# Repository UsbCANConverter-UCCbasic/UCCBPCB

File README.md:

# PCB for UsbCANConverterBasic
This is PCB for UsbCANConverter basic, designed in free software KiCad.
#License
UsbCANConverterBasic is free software: you can redistribute it and/or modify it under the terms of the GNU Lesser General Public License as published by the Free Software Foundation, either version 3 of the License, or (at your option) any later version. Project is distributed in the hope that it will be useful, but WITHOUT ANY WARRANTY; without even the implied warranty of MERCHANTABILITY or FITNESS FOR A PARTICULAR PURPOSE. See the GNU Lesser General Public License for more details.

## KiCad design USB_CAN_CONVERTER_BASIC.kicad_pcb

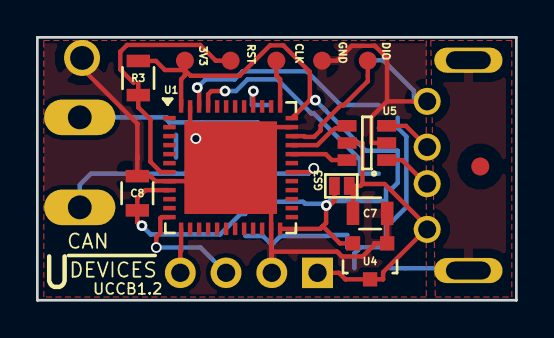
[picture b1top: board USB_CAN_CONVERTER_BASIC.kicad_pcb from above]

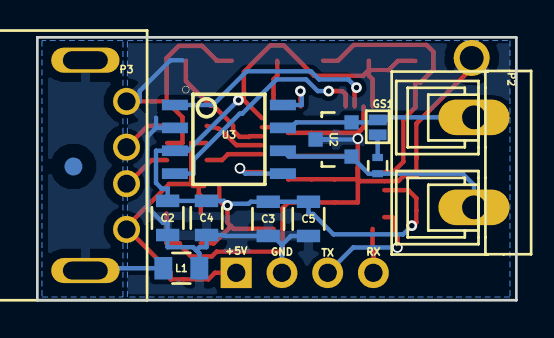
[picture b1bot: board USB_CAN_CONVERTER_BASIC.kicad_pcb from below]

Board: 2 copper layers, 26.6 x 14.6 mm, 22 parts (11 on the bottom side), 20 nets.

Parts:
C2: 100n; R_0805
C3: 10u; R_0805
C4: 10nC; R_0805
C5: 100nC; R_0805
C7, C8: 1uC; R_0805
F1: fiducial; Fiducial_1mm_Dia_2.54mm_Outer_CopperTop
F2: fiducial; Fiducial_1mm_Dia_2.54mm_Outer_CopperBottom
GS1, GS3: GS2; GS2s
L1: 30R@100MHz; C_0805
P1: CONN_01X05; swd_smd_conn5
P2: CONN_01X02; AK300-2MIRROR
P3: USB_A; USB_A_DS1097R
P4: CONN_01X04; Pin_Header_Angled_1x04m
R3: 10k; R_0805
R4: 60R; R_0402
U1: STM32F042C6Ux; QFN-48-1EP_7x7mm_Pitch0.5mm
U2: PSD2CAN; SOT-23
U3: TCAN332; SO
U4: MCP1700T-3302E/TT; SOT-23
U5: USBLC6-2; SOT-23-6

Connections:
+3V3: C2.1, C3.1, C4.1, C5.1, C8.1, GS3.2, P1.1, R3.2, U1.9, U1.24, U1.36, U1.48, U3.3, U4.2
+5V: C7.1, GS3.1, P3.1, P4.1, U4.3, U5.5
/USART_RX: P4.4, U1.13
/USART_TX: P4.3, U1.12
CAN_MOD: U1.40, U3.8
CAN_MOD2: U1.30, U3.5
CAN_RX: U1.45, U3.4
CAN_TX: U1.46, U3.1
GND: C2.2, C3.2, C4.2, C5.2, C7.2, C8.2, L1.1, P1.4, P3.4, P4.2, U1.8, U1.23, U1.35, U1.47, U1.49, U2.3, U3.2, U4.1, U5.2
unnamed: GS1.1, R4.1
unnamed: GS1.2, P2.2, U2.2, U3.7
unnamed: L1.2, P3.5
unnamed: P1.2, R3.1, U1.7
unnamed: P2.1, R4.2, U2.1, U3.6
unnamed: P3.2, U5.1
unnamed: P3.3, U5.3
unnamed: U1.32, U5.6
unnamed: U1.33, U5.4
SW_CLK: P1.3, U1.37
SW_DIO: P1.5, U1.34

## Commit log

2016-07-04 USB and CAN connector fix
2016-07-05 UART1 switch, logo creation, CAN footprint update, botom layer replacement.
    UART1 switch, logo creation, CAN footprint update, botom layer
    replacement.
2016-07-09 SWD connector update, logo generation, board otline update.
2016-07-09 CAN Jumpers addition
2016-07-11 Outline size reduction
2016-07-11 USART change
2016-07-12 Board rooting done.
2016-07-12 Thermal pad update
2016-07-12 BOM addition
2016-07-13 Rooting and CANmod replace.
2016-07-13 Gerber and drill generation
2016-07-13 BOM update
    BOM update
2016-07-18 License addition.
    License addition.
2016-08-13 Panel pcb addition and stencils.
2016-08-31 Readme update
2016-10-04 Schematic name update
    Schematic name update
2016-10-17 Update LICENSE
2016-12-08 Fiducial Add
    Fiducial Add
2016-12-08 components description update
    components description update
2016-12-09 Update Outputs
    Update Outputs
2016-12-27 Gerber update
    Gerber update
2017-01-23 gerber updates
2023-07-11 Create 3dmodel
    So people can download a 3d model of this great project.
